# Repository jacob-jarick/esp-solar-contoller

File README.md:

# esp-solar-contoller

esp8266 and esp32 based solar controllers targetting Houses with a fronius solar system (other inverters can be supported).

Inspired by the various DIY powerwalls

https://www.facebook.com/groups/diypowerwalls/

## Use

Common Day devices:

* Pool Pump
* powerwall / UPS / Battery Bank charger
* roof exhuast fan

Common Night time Devices:

* UPS mains disconnect
* Grid tie inverter turn on

## Example Applications

**Simple**

(day) Turn on day time device when PV export is greater than device size (eg pool pump)

**DIY Powerwall**

(Day) Turn on charger when PV export is greater than charger size.

(night) Turn on inverter when power import is larger than inverter size.

**UPS**

(Day) Turn on charger when PV export is greater than charger size.

(night) disconnect UPS mains if house is drawing power from the grid.

## Features

* Self hosted solution, no external servers needed everything runs on the microchip.
* Complete Web Interface for confguration and monitoring.
* JSON config file for easy manual editing.
* OLED display
* Support querying Fronius inverters directly
* NTP time sync
* Fallback WiFi network settings.

### Battery Monitoring (esp32)

* High voltage disconect (day)
* Low Cell Voltage disconnect (night)
* High temp shutdown

## esp8266

Supporrt for all common esp8266 boards.

* sonoff
* IoT Yunshun
* Anything tasmota runs on.

Supports adding OLED display the above.

## ESP32 Board

Custom designed board.

* 16 Bit 4 channel ADC fed to 4 8x analog signal multiplexers allowing for a total of 32 analog lines.

* 16 Voltage monitoring lines.
* 16 ntc temp sensors + 1 ambient temp sensor.
* SD Card for config storage.
* Simple Oled display.
* Piezo buzzer.
* 5v & 3.3v i2c headers for expansion.

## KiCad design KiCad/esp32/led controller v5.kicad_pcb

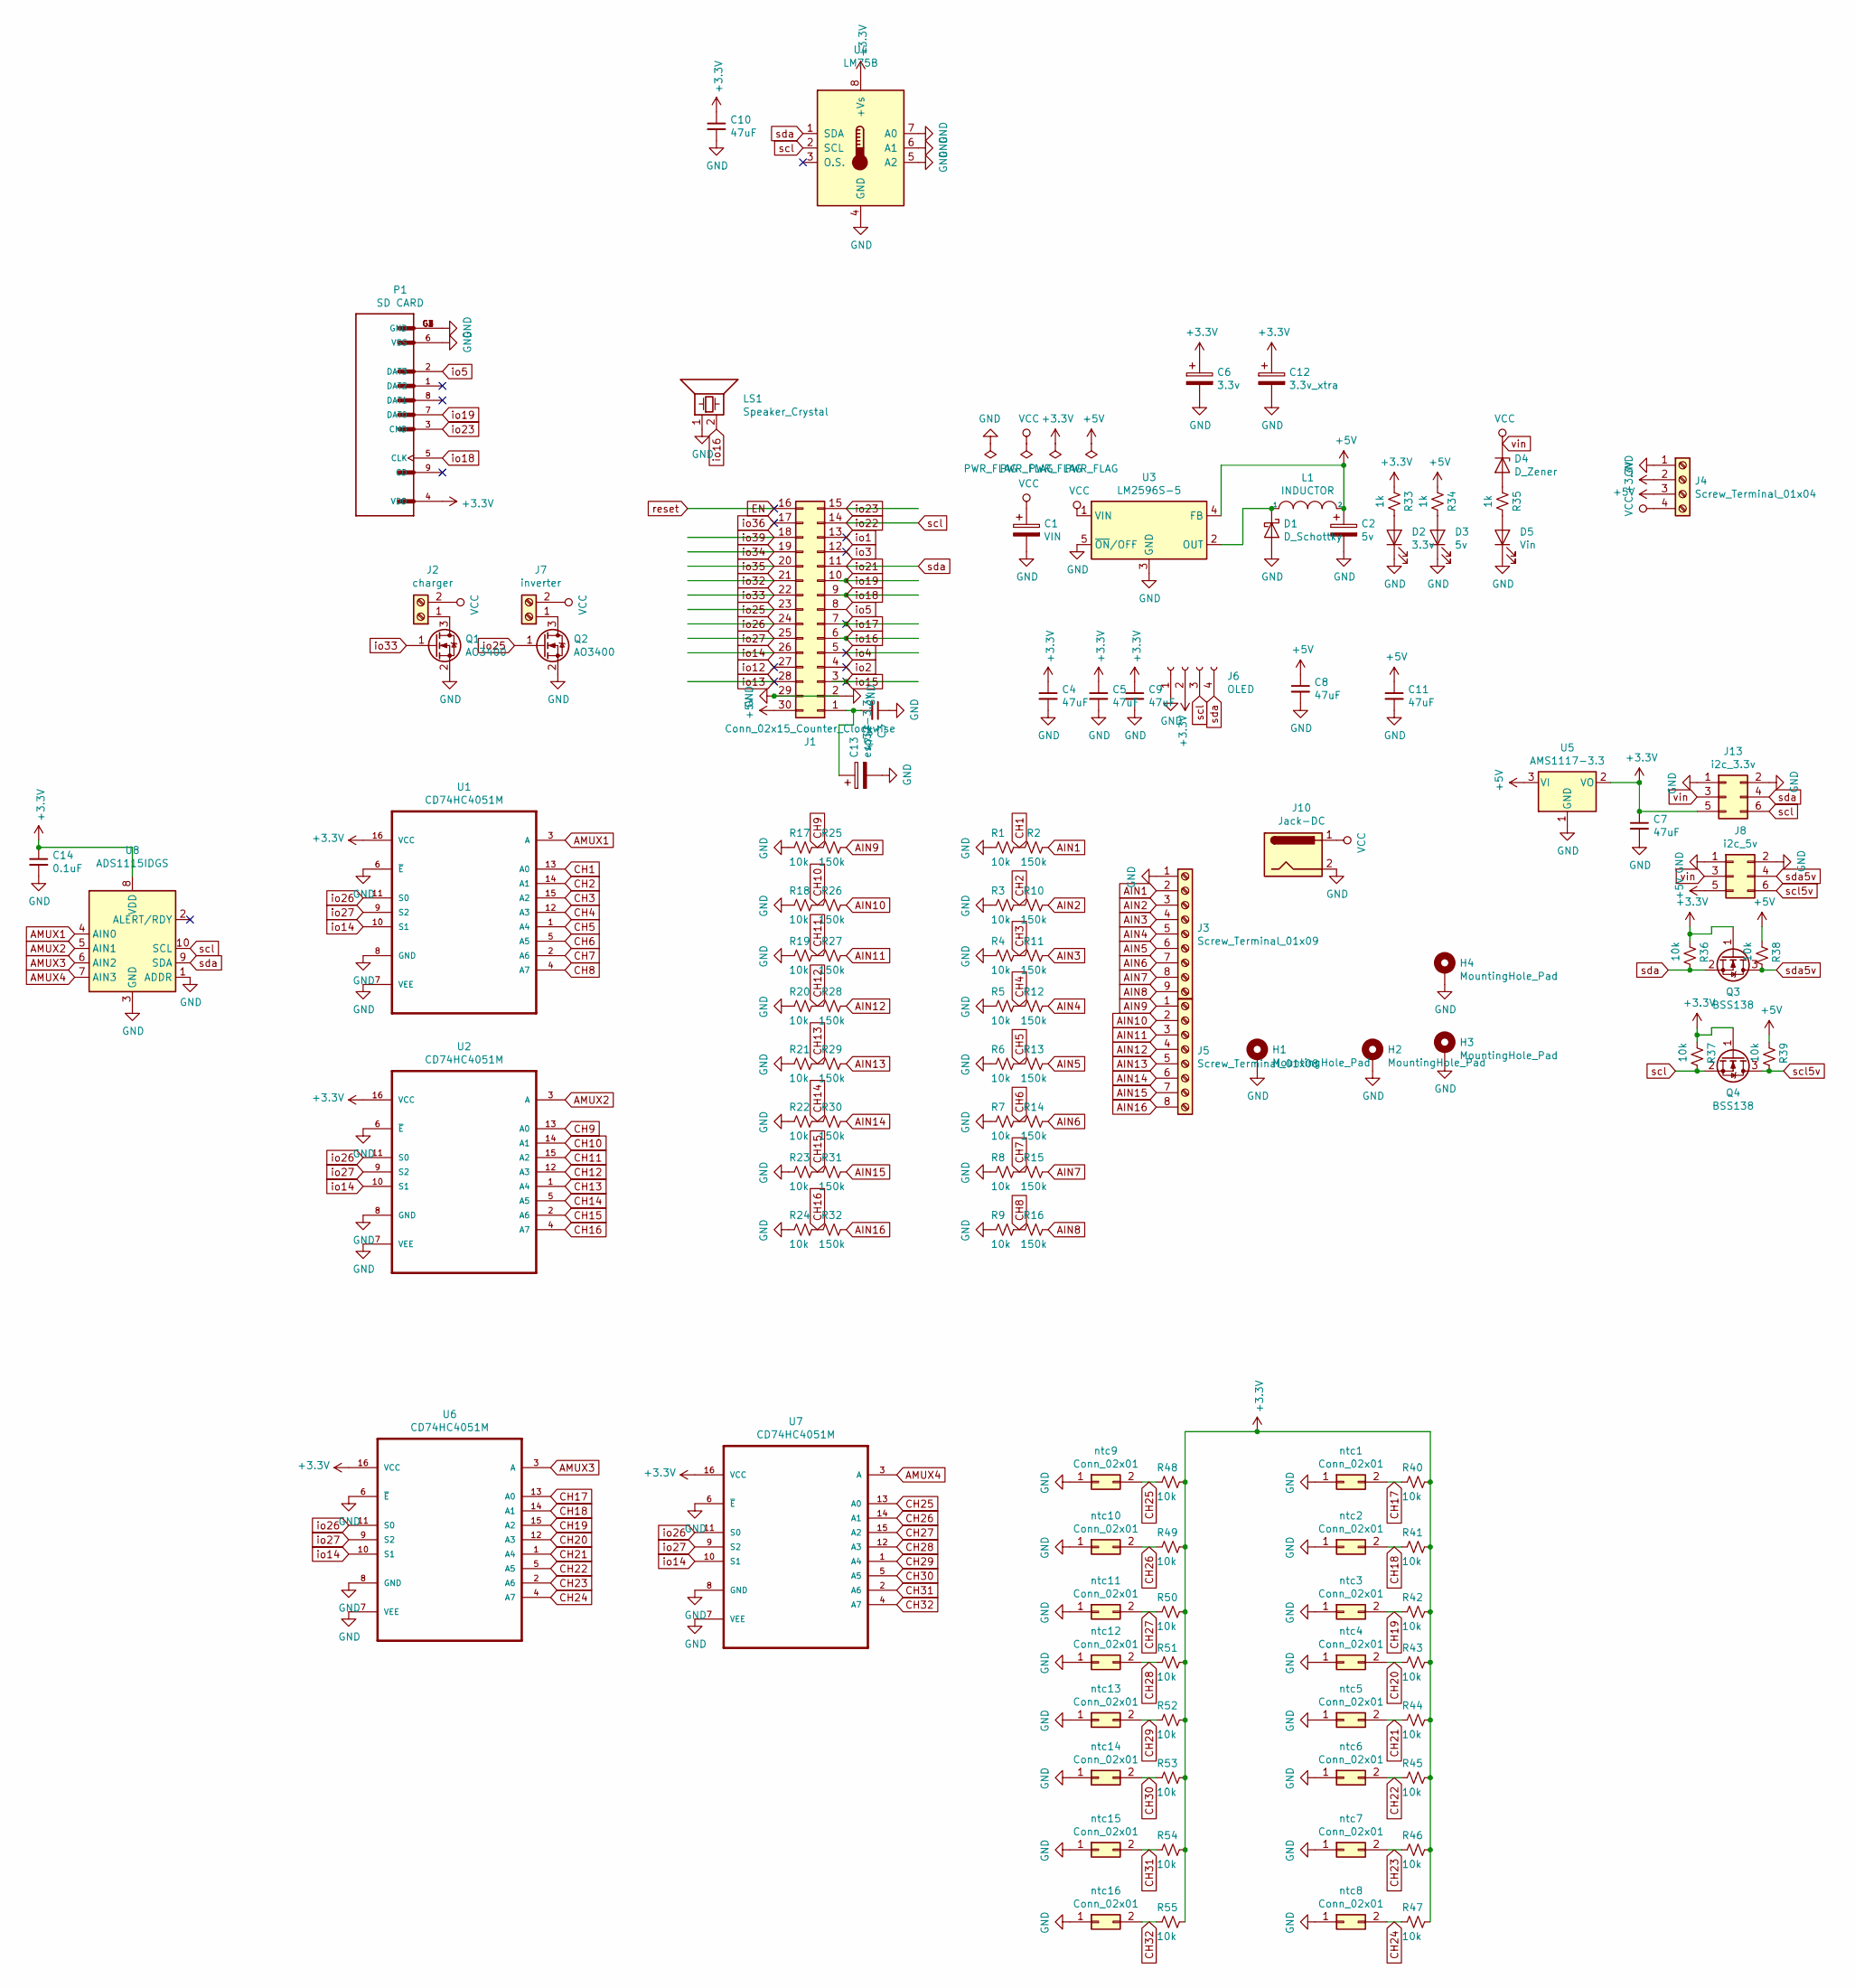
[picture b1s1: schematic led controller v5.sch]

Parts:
C1: VIN; CP_Radial_D10.0mm_P7.50mm
C2: 5v; CP_Radial_D10.0mm_P7.50mm
C3, C4, C5, C7, C8, C9, C10, C11: 47uF; C_0805_2012Metric_Pad1.15x1.40mm_HandSolder
C6: 3.3v; CP_Radial_D10.0mm_P7.50mm
C12: 3.3v_xtra; CP_Radial_D10.0mm_P7.50mm
C13: esp32-3.3v; CP_Radial_D10.0mm_P7.50mm
C14: 0.1uF; C_0805_2012Metric_Pad1.15x1.40mm_HandSolder
D1: D_Schottky; D_SMA_Handsoldering
D2: 3.3v; LED_1206_3216Metric_Pad1.42x1.75mm_HandSolder
D3: 5v; LED_1206_3216Metric_Pad1.42x1.75mm_HandSolder
D4: D_Zener; D_SOD-323F
D5: Vin; LED_1206_3216Metric_Pad1.42x1.75mm_HandSolder
H1, H2, H3, H4: MountingHole_Pad; MountingHole_3.2mm_M3_Pad_Via
J1: Conn_02x15_Counter_Clockwise; esp32-devkit-v1
J2: charger; PhoenixContact_MCV_1,5_2-G-3.81_1x02_P3.81mm_Vertical
J3: Screw_Terminal_01x09; PhoenixContact_MCV_1,5_9-G-3.81_1x09_P3.81mm_Vertical
J4: Screw_Terminal_01x04; PhoenixContact_MCV_1,5_4-G-3.81_1x04_P3.81mm_Vertical
J5: Screw_Terminal_01x08; PhoenixContact_MCV_1,5_8-G-3.81_1x08_P3.81mm_Vertical
J6: OLED; PinHeader_1x04_P2.54mm_Vertical
J7: inverter; PhoenixContact_MCV_1,5_2-G-3.81_1x02_P3.81mm_Vertical
J8: i2c_5v; i2c-Header-5v
J10: Jack-DC; BarrelJack_Horizontal
J13: i2c_3.3v; i2c-Header
L1: INDUCTOR; L_Taiyo-Yuden_MD-5050
LS1: Speaker_Crystal; Buzzer_15x7.5RM7.6
P1: SD CARD; SUNTECH_ST-TF-003A
Q1, Q2: AO3400; SOT-23
Q3, Q4: BSS138; SOT-23
R1, R3, R4, R5, R6, R7, R8, R9, R17, R18, R19, R20, R21, R22, R23, R24, R36, R37, R38, R39, R40, R41, R42, R43, R44, R45, R46, R47, R48, R49, R50, R51, R52, R53, R54, R55: 10k; R_0805_2012Metric_Pad1.15x1.40mm_HandSolder
R2, R10, R11, R12, R13, R14, R15, R16, R25, R26, R27, R28, R29, R30, R31, R32: 150k; R_0805_2012Metric_Pad1.15x1.40mm_HandSolder
R33, R34, R35: 1k; R_0805_2012Metric_Pad1.15x1.40mm_HandSolder
U1, U2, U6, U7: CD74HC4051M; STC_SOP-16_3.9x9.9mm_P1.27mm
U3: LM2596S-5; TO-263-5_TabPin3
U4: LM75B; SOIC-8_3.9x4.9mm_P1.27mm
U5: AMS1117-3.3; SOT-223-3_TabPin2
U8: ADS1115IDGS; TSSOP-10_3x3mm_P0.5mm
ntc1, ntc2, ntc3, ntc4, ntc5, ntc6, ntc7, ntc8, ntc9, ntc10, ntc11, ntc12, ntc13, ntc14, ntc15, ntc16: Conn_02x01; PinHeader_1x02_P2.54mm_Vertical

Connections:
+3V3: C4.1, C5.1, C6.1, C7.1, C9.1, C10.1, C12.1, C14.1, J4.2, J6.2, J13.5, P1.4 (VDD), Q3.1 (G), Q4.1 (G), R33.1, R36.2, R37.2, R40.1, R41.1, R42.1, R43.1, R44.1, R45.1, R46.1, R47.1, R48.1, R49.1, R50.1, R51.1, R52.1, R53.1, R54.1, R55.1, U1.16 (VCC), U2.16 (VCC), U4.8 (+Vs), U5.2 (VO), U6.16 (VCC), U7.16 (VCC), U8.8 (VDD)
+5V: C2.1, C8.1, C11.1, J1.30, J4.3, J8.5, L1.2, R34.1, R38.2, R39.2, U3.4 (FB), U5.3 (VI)
AIN1: J3.2, R2.2
AIN2: J3.3, R10.2
AIN3: J3.4, R11.2
AIN4: J3.5, R12.2
AIN5: J3.6, R13.2
AIN6: J3.7, R14.2
AIN7: J3.8, R15.2
AIN8: J3.9, R16.2
AIN9: J5.1, R25.2
AIN10: J5.2, R26.2
AIN11: J5.3, R27.2
AIN12: J5.4, R28.2
AIN13: J5.5, R29.2
AIN14: J5.6, R30.2
AIN15: J5.7, R31.2
AIN16: J5.8, R32.2
AMUX1: U1.3 (A), U8.4 (AIN0)
AMUX2: U2.3 (A), U8.5 (AIN1)
AMUX3: U6.3 (A), U8.6 (AIN2)
AMUX4: U7.3 (A), U8.7 (AIN3)
CH1: R1.1, R2.1, U1.13 (A0)
CH2: R3.1, R10.1, U1.14 (A1)
CH3: R4.1, R11.1, U1.15 (A2)
CH4: R5.1, R12.1, U1.12 (A3)
CH5: R6.1, R13.1, U1.1 (A4)
CH6: R7.1, R14.1, U1.5 (A5)
CH7: R8.1, R15.1, U1.2 (A6)
CH8: R9.1, R16.1, U1.4 (A7)
CH9: R17.1, R25.1, U2.13 (A0)
CH10: R18.1, R26.1, U2.14 (A1)
CH11: R19.1, R27.1, U2.15 (A2)
CH12: R20.1, R28.1, U2.12 (A3)
CH13: R21.1, R29.1, U2.1 (A4)
CH14: R22.1, R30.1, U2.5 (A5)
CH15: R23.1, R31.1, U2.2 (A6)
CH16: R24.1, R32.1, U2.4 (A7)
CH17: R40.2, U6.13 (A0), ntc1.2
CH18: R41.2, U6.14 (A1), ntc2.2
CH19: R42.2, U6.15 (A2), ntc3.2
CH20: R43.2, U6.12 (A3), ntc4.2
CH21: R44.2, U6.1 (A4), ntc5.2
CH22: R45.2, U6.5 (A5), ntc6.2
CH23: R46.2, U6.2 (A6), ntc7.2
CH24: R47.2, U6.4 (A7), ntc8.2
CH25: R48.2, U7.13 (A0), ntc9.2
CH26: R49.2, U7.14 (A1), ntc10.2
CH27: R50.2, U7.15 (A2), ntc11.2
CH28: R51.2, U7.12 (A3), ntc12.2
CH29: R52.2, U7.1 (A4), ntc13.2
CH30: R53.2, U7.5 (A5), ntc14.2
CH31: R54.2, U7.2 (A6), ntc15.2
CH32: R55.2, U7.4 (A7), ntc16.2
EN: J1.16
GND: C1.2, C2.2, C3.1, C4.2, C5.2, C6.2, C7.2, C8.2, C9.2, C10.2, C11.2, C12.2, C13.2, C14.2, D1.2 (A), D2.1 (K), D3.1 (K), D5.1 (K), H1.1, H2.1, H3.1, H4.1, J1.2, J1.29, J3.1, J4.1, J6.1, J8.1, J8.2, J10.2, J13.1, J13.2, LS1.1, P1.6 (VSS), P1.G1 (GND), P1.G2 (GND), P1.G3 (GND), P1.G4 (GND), Q1.2 (S), Q2.2 (S), R1.2, R3.2, R4.2, R5.2, R6.2, R7.2, R8.2, R9.2, R17.2, R18.2, R19.2, R20.2, R21.2, R22.2, R23.2, R24.2, U1.6 (~E), U1.7 (VEE), U1.8 (GND), U2.6 (~E), U2.7 (VEE), U2.8 (GND), U3.3 (GND), U3.5 (~ON~/OFF), U4.4 (GND), U4.5 (A2), U4.6 (A1), U4.7 (A0), U5.1 (GND), U6.6 (~E), U6.7 (VEE), U6.8 (GND), U7.6 (~E), U7.7 (VEE), U7.8 (GND), U8.1 (ADDR), U8.3 (GND), ntc1.1, ntc2.1, ntc3.1, ntc4.1, ntc5.1, ntc6.1, ntc7.1, ntc8.1, ntc9.1, ntc10.1, ntc11.1, ntc12.1, ntc13.1, ntc14.1, ntc15.1, ntc16.1
unnamed: C3.2, C13.1, J1.1
unnamed: D1.1 (K), L1.1, U3.2 (OUT)
unnamed: D2.2 (A), R33.2
unnamed: D3.2 (A), R34.2
unnamed: D4.2 (A), R35.1
unnamed: D5.2 (A), R35.2
unnamed: J2.1, Q1.3 (D)
unnamed: J7.1, Q2.3 (D)
io1: J1.13
io2: J1.4
io3: J1.12
io4: J1.5
io5: J1.8, P1.2 (DAT3)
io12: J1.27
io13: J1.28
io14: J1.26, U1.10 (S1), U2.10 (S1), U6.10 (S1), U7.10 (S1)
io15: J1.3
io16: J1.6, LS1.2
io17: J1.7
io18: J1.9, P1.5 (CLK)
io19: J1.10, P1.7 (DAT0)
io21: J1.11, J6.4, J13.4, Q3.2 (S), R36.1, U4.1 (SDA), U8.9 (SDA)
io22: J1.14, J6.3, J13.6, Q4.2 (S), R37.1, U4.2 (SCL), U8.10 (SCL)
io23: J1.15, P1.3 (CMD)
io25: J1.23, Q2.1 (G)
io26: J1.24, U1.11 (S0), U2.11 (S0), U6.11 (S0), U7.11 (S0)
io27: J1.25, U1.9 (S2), U2.9 (S2), U6.9 (S2), U7.9 (S2)
io32: J1.21
io33: J1.22, Q1.1 (G)
io34: J1.19
io35: J1.20
io36: J1.17
io39: J1.18
scl5v: J8.6, Q4.3 (D), R39.1
sda5v: J8.4, Q3.3 (D), R38.1
vin: C1.1, D4.1 (K), J2.2, J4.4, J7.2, J8.3, J10.1, J13.3, U3.1 (VIN)

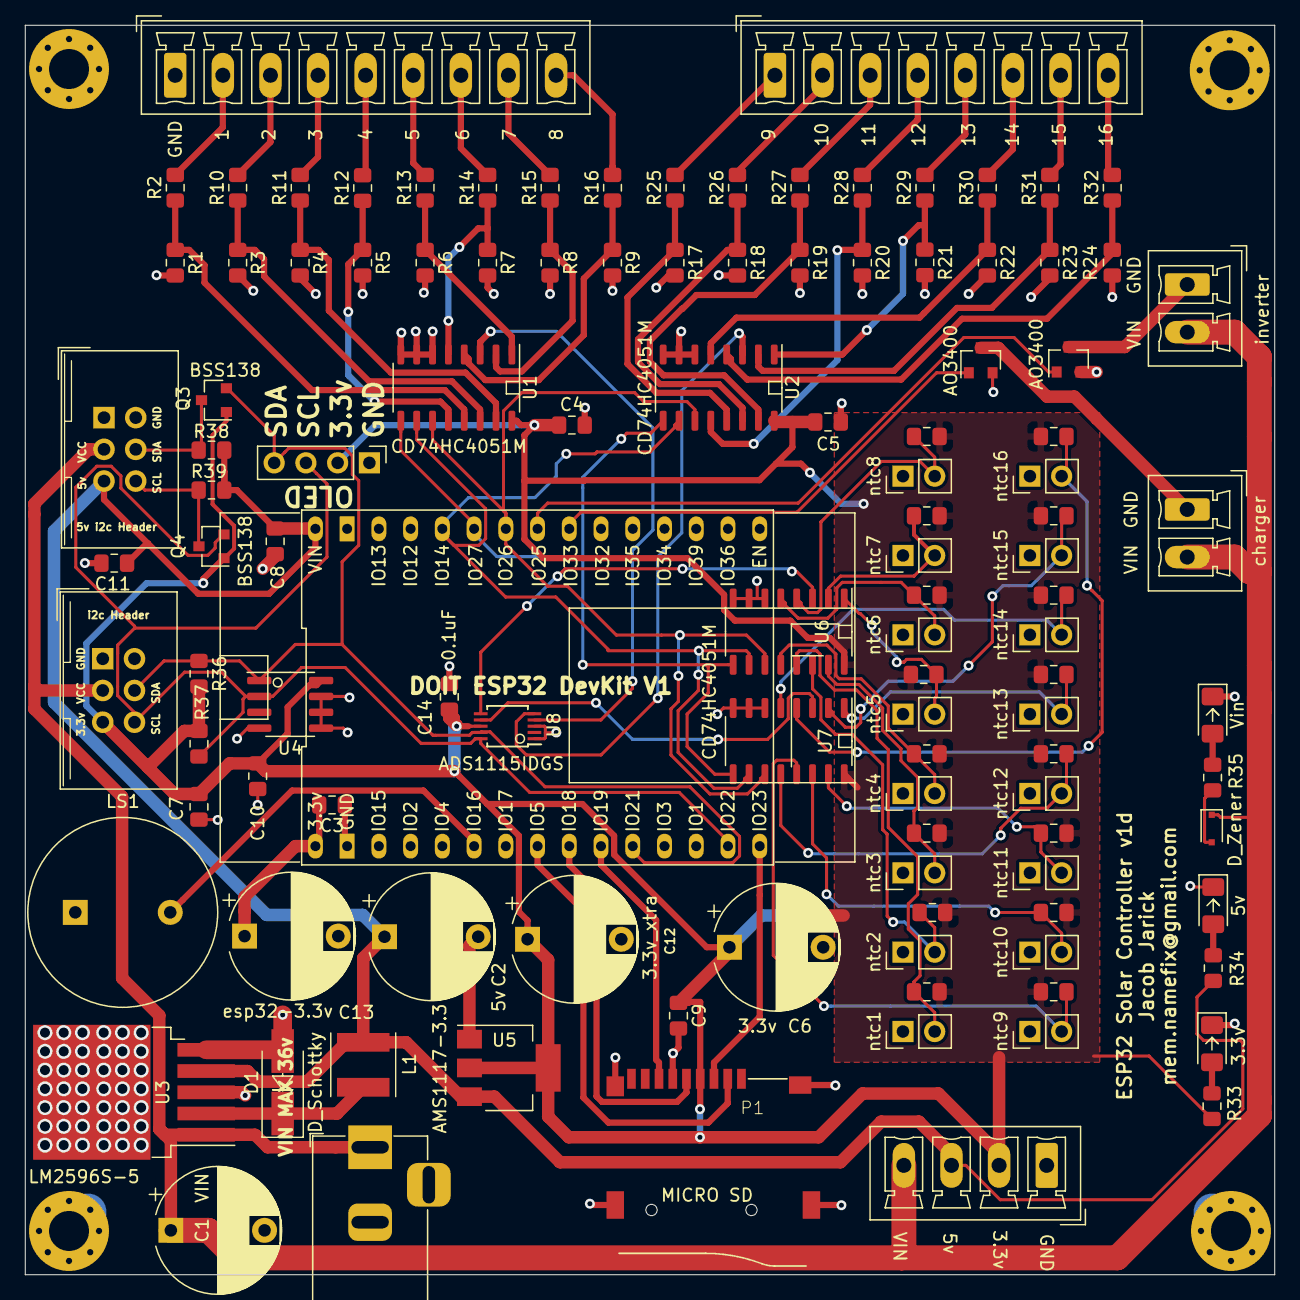
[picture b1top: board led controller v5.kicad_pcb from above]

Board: 2 copper layers, 100.0 x 100.0 mm, 119 parts (0 on the bottom side), 78 nets.

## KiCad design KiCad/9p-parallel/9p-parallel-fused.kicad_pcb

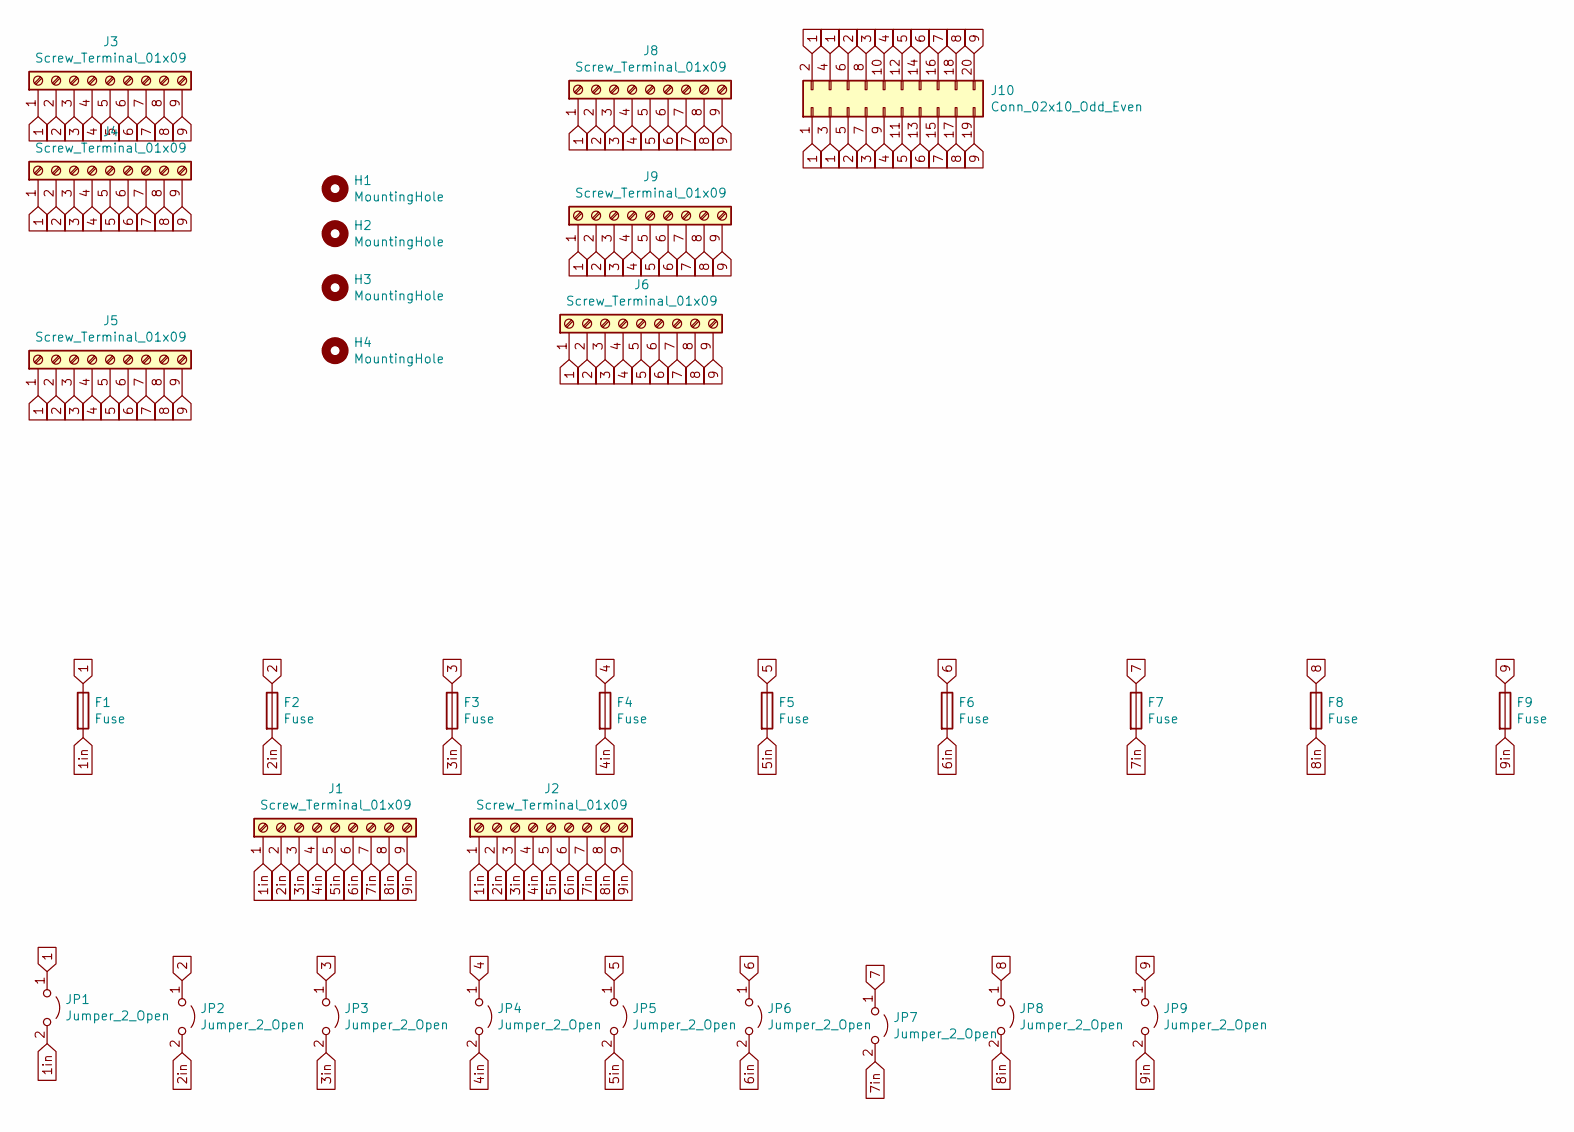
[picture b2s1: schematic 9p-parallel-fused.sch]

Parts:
F1, F2, F3, F4, F5, F6, F7, F8, F9: Fuse; Fuseholder_Cylinder-5x20mm_Stelvio-Kontek_PTF78_Horizontal_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
H1, H2, H3, H4: MountingHole; MountingHole_4.3mm_M4_ISO14580
J1: Screw_Terminal_01x09; PhoenixContact_MC_1,5_9-G-5.08_1x09_P5.08mm_Horizontal-larg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
J2, J6, J8, J9: Screw_Terminal_01x09; PhoenixContact_MCV_1,5_9-G-3.81_1x09_P3.81mm_Vertical
J3, J4, J5: Screw_Terminal_01x09; PhoenixContact_MCV_1,5_9-G-5.08_1x09_P5.08mm_Vertical-large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
J10: Conn_02x10_Odd_Even; IDC-Header_2x10_P2.54mm_Vertical
JP1, JP2, JP3, JP4, JP5, JP6, JP7, JP8, JP9: Jumper_2_Open; SolderJumper-2_P1.3mm_Open_Pad1.0x1.5mm

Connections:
1: F1.1, J3.1, J4.1, J5.1, J6.1, J8.1, J9.1, J10.1, J10.2, J10.3, J10.4, JP1.1 (A)
1in: F1.2, J1.1, J2.1, JP1.2 (B)
2: F2.1, J3.2, J4.2, J5.2, J6.2, J8.2, J9.2, J10.5, J10.6, JP2.1 (A)
2in: F2.2, J1.2, J2.2, JP2.2 (B)
3: F3.1, J3.3, J4.3, J5.3, J6.3, J8.3, J9.3, J10.7, J10.8, JP3.1 (A)
3in: F3.2, J1.3, J2.3, JP3.2 (B)
4: F4.1, J3.4, J4.4, J5.4, J6.4, J8.4, J9.4, J10.9, J10.10, JP4.1 (A)
4in: F4.2, J1.4, J2.4, JP4.2 (B)
5: F5.1, J3.5, J4.5, J5.5, J6.5, J8.5, J9.5, J10.11, J10.12, JP5.1 (A)
5in: F5.2, J1.5, J2.5, JP5.2 (B)
6: F6.1, J3.6, J4.6, J5.6, J6.6, J8.6, J9.6, J10.13, J10.14, JP6.1 (A)
6in: F6.2, J1.6, J2.6, JP6.2 (B)
7: F7.1, J3.7, J4.7, J5.7, J6.7, J8.7, J9.7, J10.15, J10.16, JP7.1 (A)
7in: F7.2, J1.7, J2.7, JP7.2 (B)
8: F8.1, J3.8, J4.8, J5.8, J6.8, J8.8, J9.8, J10.17, J10.18, JP8.1 (A)
8in: F8.2, J1.8, J2.8, JP8.2 (B)
9: F9.1, J3.9, J4.9, J5.9, J6.9, J8.9, J9.9, J10.19, J10.20, JP9.1 (A)
9in: F9.2, J1.9, J2.9, JP9.2 (B)

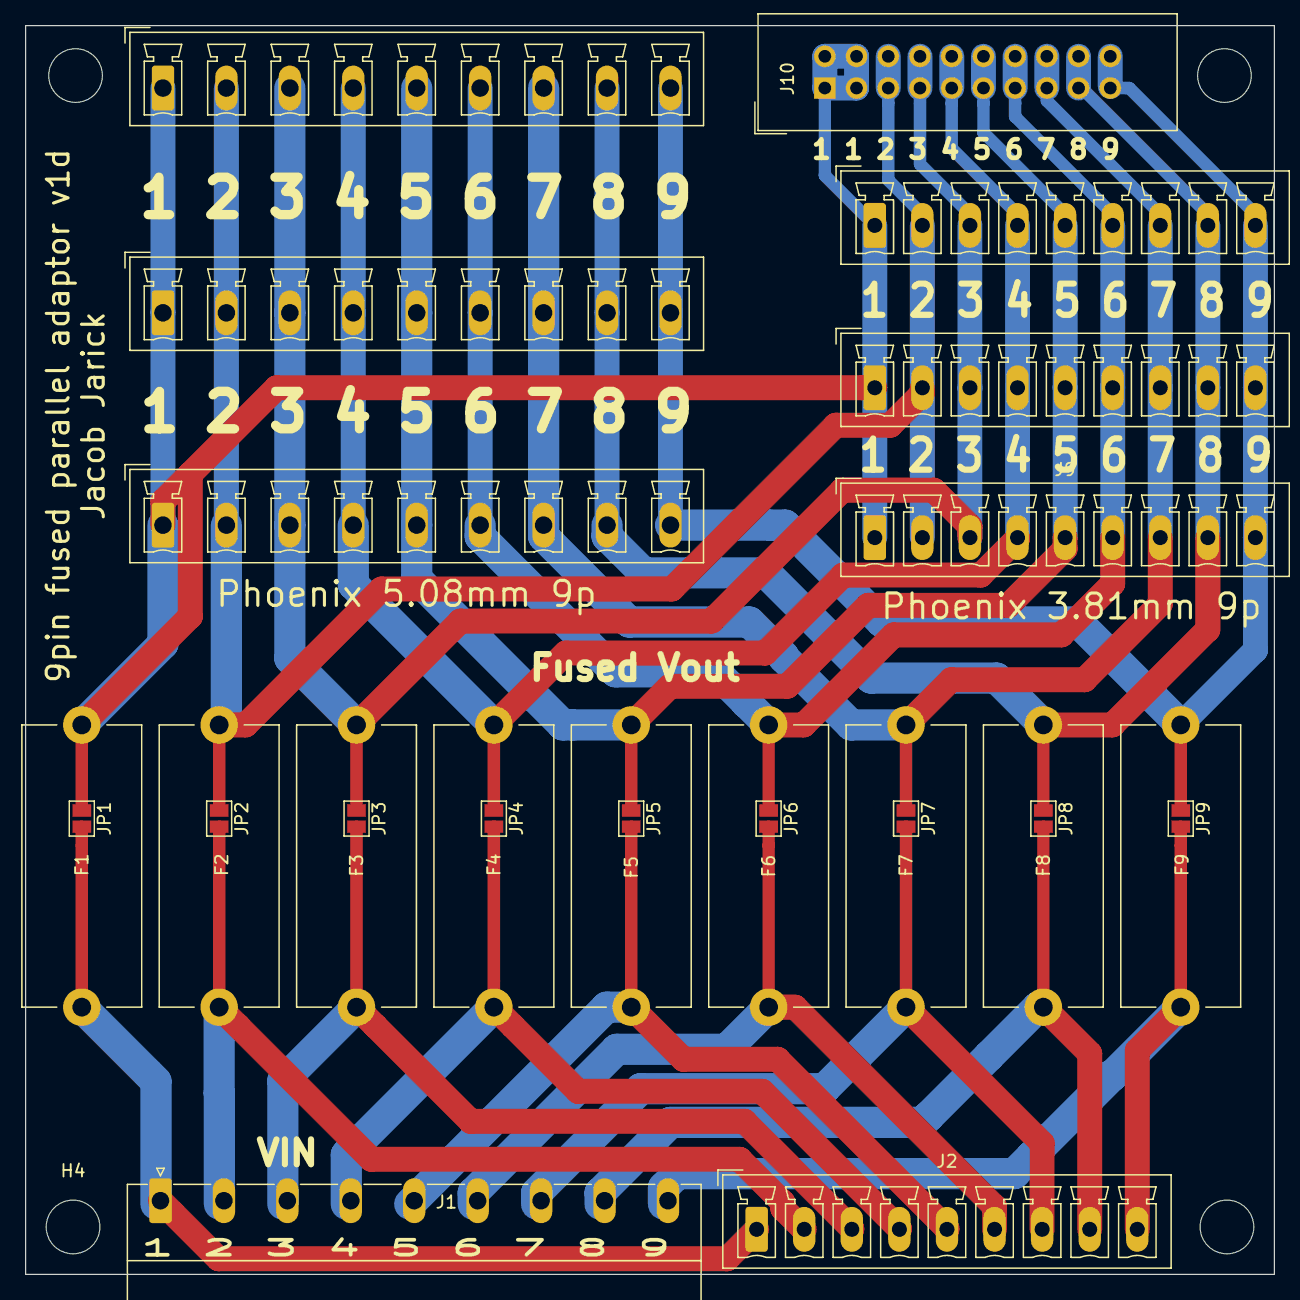
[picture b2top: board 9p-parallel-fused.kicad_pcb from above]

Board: 2 copper layers, 100.0 x 100.0 mm, 31 parts (0 on the bottom side), 18 nets.

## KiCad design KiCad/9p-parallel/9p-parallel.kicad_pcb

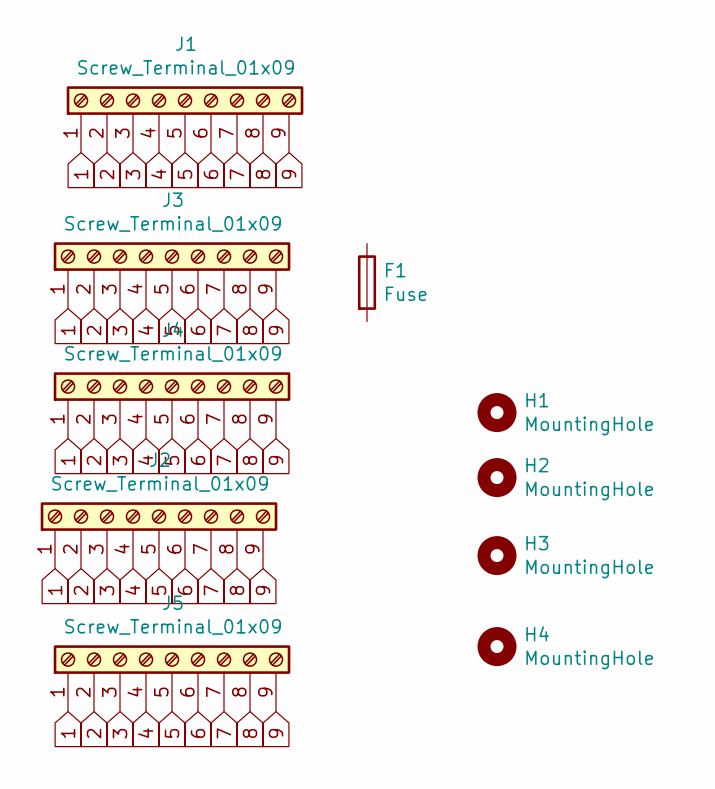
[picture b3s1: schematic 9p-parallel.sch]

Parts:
F1: Fuse; Fuseholder_Cylinder-5x20mm_Stelvio-Kontek_PTF78_Horizontal_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
H1, H2, H3, H4: MountingHole; MountingHole_4.3mm_M4_ISO14580
J1: Screw_Terminal_01x09; PhoenixContact_MC_1,5_9-G-5.08_1x09_P5.08mm_Horizontal
J2, J3, J4, J5: Screw_Terminal_01x09; PhoenixContact_MCV_1,5_9-G-5.08_1x09_P5.08mm_Vertical

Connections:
1: J1.1, J2.1, J3.1, J4.1, J5.1
2: J1.2, J2.2, J3.2, J4.2, J5.2
3: J1.3, J2.3, J3.3, J4.3, J5.3
4: J1.4, J2.4, J3.4, J4.4, J5.4
5: J1.5, J2.5, J3.5, J4.5, J5.5
6: J1.6, J2.6, J3.6, J4.6, J5.6
7: J1.7, J2.7, J3.7, J4.7, J5.7
8: J1.8, J2.8, J3.8, J4.8, J5.8
9: J1.9, J2.9, J3.9, J4.9, J5.9

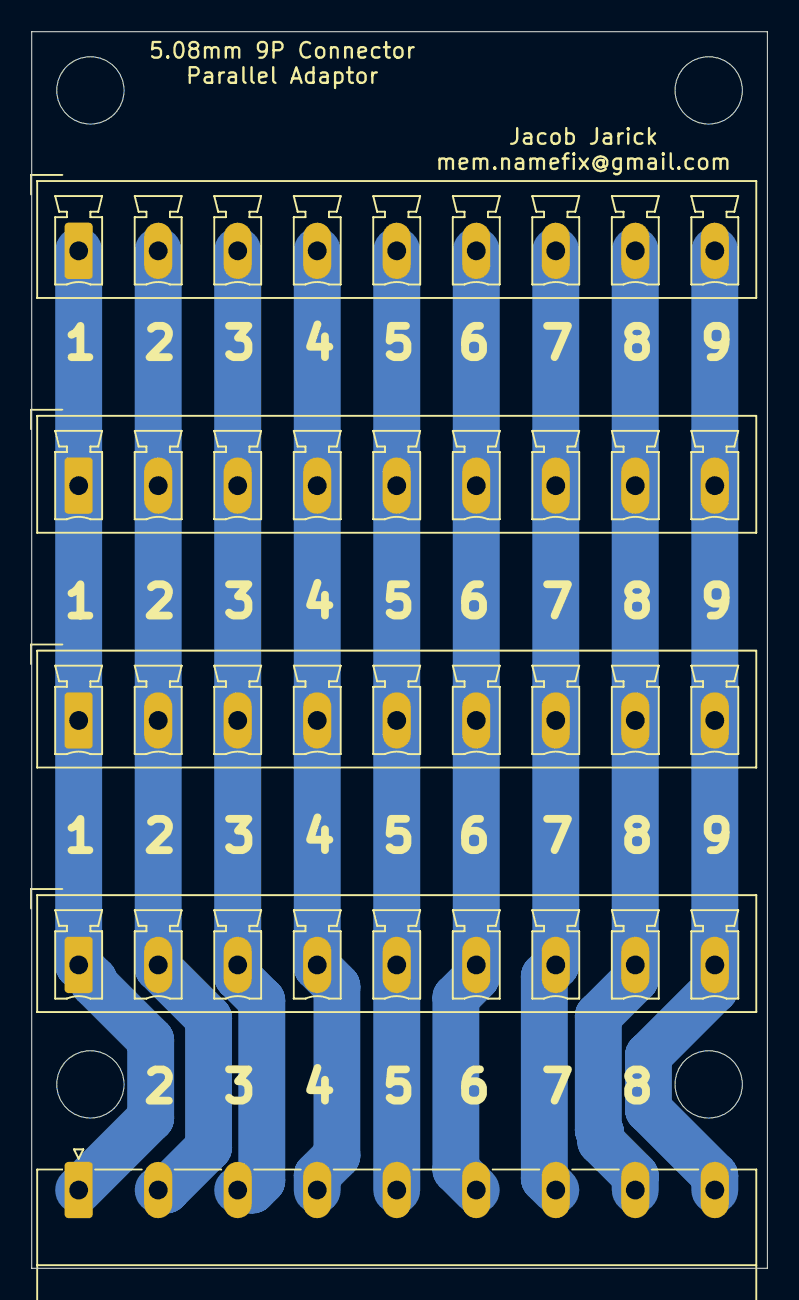
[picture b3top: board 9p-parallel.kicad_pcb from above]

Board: 2 copper layers, 47.0 x 79.0 mm, 9 parts (0 on the bottom side), 9 nets.

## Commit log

2020-02-28 source push
2020-02-28 shell scripts
2020-02-28 added shell scripts for publishing firmwares
2020-02-28 tidy up
2020-02-28 tidy
2020-03-02 update code for ads1115.
2020-03-02 adc code, html examples
2020-03-02 fixes to support latest esp32 arduino release.
    adc - set gain etc after inlcude ads11115
    ESP32HTTPUpdate - old httpupdate no longer works, fixes applied.
    maths - float_max - ESP32HTTPUpdate (among others) undef Arduino min and max. easiest fix is to provide my own function.
    webpages - toDouble not a string member anymore ? or never was. fixed.
    HTTPClient - argument syntax has changed for esp32 lib - fixed.
2020-03-03 cleanup
2020-03-03 update.ino - fix html loop if unable to fetch file
2020-03-05 consts
2020-03-06 i2c is buggy on latest board. slowed down bus speed
2020-03-06 ntc stuff
2020-03-06 ntc work
2020-03-07 ntc fix
2020-03-07 adc battery fix
2020-03-07 networking fixes.
2020-03-07 update logic, adc, ports, save config optimization
2020-03-13 battery calibration
2020-03-15 battery + temp
    battery calibration page added.
    ntc temp max changed to uint8_t
2020-03-15 maths max, ping sd, night time logic
2020-03-16 24/7 mode added
    same as setting charger and inverter time slots to 12-12
2020-03-16 update html fix
2020-03-16 battery calibrate JS moved to battery page
2020-03-16 updated ESP32 board
2020-03-16 images
2020-03-16 Update esp32_solar_controller.ino
    24/7 - idle between device swaps.
    mode reason message text cleaned up
2020-03-16 removing msg.txt
2020-03-16 remove all traces of frline
    handy for esp8266 due to lack of progmem space, for esp32 it just makes things harder to follow.
2020-03-16 latest firmware
2020-03-17 modeset fix
2020-03-18 consts, mode message
2020-03-29 fsfree removed, random delays added for same mode
2020-03-30 removed pcf support. small tidy up
2020-03-31 battery_msg removed.
2020-03-31 fixes
2020-03-31 system_msgs
2020-03-31 size_system_msgs
2020-04-01 download_html
    trigger if FW versions are different.
    moved bool to flags from config.
2020-04-01 type fix
2020-04-02 get_url & get_url_and_save
2020-04-02 fronius fix
2020-04-02 strings
2020-04-09 adc polling
    much more efficient ADC checking.
2020-04-09 adc poll timer
2020-04-09 rm volt_synced flag
2020-04-09 phase voltage monitoring
2020-04-09 idle fix
2020-04-09 maths, time.
2020-04-09 time compare fix
2020-04-09 overflow fix
2020-04-10 remove adc_read
    access array directly
2020-04-10 adc_enable
    skip ADC reads on disabled channels
2020-04-10 adc_enable
2020-04-12 removed battery_volt_idl & battery_volt_over
2020-04-12 latest fw
2020-04-12 fronius 3phase work
2020-04-19 QuickMedianLib
2020-05-04 Ads1115_mux lib
2020-05-04 Ads1115_mux library
    WIP.
    compiles clean.
2020-05-04 Ads1115_mux
2020-05-08 remove QuickMedianLib dep
    using bubble sort
2020-05-08 Ads1115_mux optmizations
2020-05-08 Ads1115_mux::digital_write
2020-05-08 var cleanup
2020-05-09 maths to libary
2020-05-09 shutdown_htemp optimization
2020-05-11 rm ntc_temp_mods
    accurate enough, also makes config.jsn smaller
    extra msg info
2020-05-12 html cleanup
2020-05-18 arduino JSON lib update
2020-06-01 lm75a code added
2020-06-01 lm75a temp displayed on oled
2020-07-08 warnings and docs
2020-07-19 ads1015 support added
2020-07-30 messages
2020-08-03 micro board. esp8266 firmware refresh
2020-08-05 fw 27
2020-08-10 bool adc_found
2020-08-10 f(!adsmux.adc_found)
2020-08-16 Oled Display Options
2020-08-17 led, stats
    fixed led modes.
    added energy display options.
2020-08-17 Cost Per Kwh
2020-08-26 ntc temp, usage tracking
2020-08-26 alarm tweak
2020-08-27 Idle When Export<
2020-08-27 fronius new day tracking
2020-08-31 fronius timestap checks
2020-09-02 tidy update code
2020-09-03 i2c_check
2020-09-03 ADC checks
    if monitor temp or voltage enabled and ADC not found force IDLE.
2020-09-03 fronius time fix
2020-09-03 proper averaging for phase sum
2020-09-11 div by 0 fix
2020-09-23 prefer DC option added
2020-10-04 strings and mode tracking
2020-10-07 favour DC
    updates and tweaks
2020-10-19 fw 183
2020-10-21 force_refresh
2020-10-21 ADC tweak
2020-10-21 web stuff
2020-11-03 fw 188 both_on mode set
2020-11-24 min off time.
    mainly code to support my bore pump.
2020-12-01 HV/ LV msgs
2020-12-01 fw 198 - log manual mode
2020-12-04 docs - diagram
2020-12-04 docs - diagrams
2020-12-15 fw 199
2020-12-15 fw 200
    small update
2021-01-03 fw 201.
    log messages
2021-01-04 mime fixes
2021-01-05 config validation
2021-01-07 syslog hostname
2021-01-11 system messages shifted to footer
2021-01-13 swapped to common header
2021-02-06 libs updated
2021-09-20 working on Lib updates.
2021-09-20 dummy
2021-09-20 dummy2
2021-09-23 fw 228.
    had to roll back o esp32 board libs 1.0.6 - issue with SD card in 2.0.0
2021-09-27 FW 229
    increased analog cell count to 32
    SD_setup.sh
2021-09-27 fix ads1115 setup
2021-09-29 fw 232
    remove hard coded limits to max cell count
2021-09-29 fw 242
    gutted NTC code, has not been used.
2021-10-13 pub url on github
2021-10-13 pub URL
2021-10-13 JSON config pretty print.
    Pub update dir.
2021-10-13 cv.txt
2021-10-13 html download debug
2021-10-19 web formatting
2021-10-26 calc_energy_usage
    moved energy used calculation to its own sub.
    called from check_grid
2021-10-29 fixes, single phase updates.
    get_watts - should work with single phase better
    calc_energy_usage - uses its own timer.
2021-11-06 added new oled display mode
2021-11-06 fw number bump
2021-11-06 3phase/single phase updates
2021-11-06 fw 244
2021-11-06 245
    whitespaces
2021-11-06 number formatting
2021-11-09 fw 247
    mostly whitespace fixes
2021-11-09 fw 247
    mostly white space fixes
2021-11-11 voltage tracking
2021-11-11 fix min AC voltage tracking
2021-11-11 update code cleaned up
2021-11-19 about to break adsmux for mcp3021
2021-11-20 adc mux code update complete..
    backwards compatible with v3 board mux.
    must set ADS1x15type and MUXType in system settings.
2021-11-21 fw 278
2021-11-21 fw 282
2021-11-23 user can toggle ain averaging
2021-11-24 optimize adc mux polling code
2021-11-24 BUGFIX - pin select in adc poll was wonky
2021-11-25 adc code tweaks. esp board libs 2.0.1
2021-11-26 roll back to 1.0.6 of esp32 board libs
    issues with SPI and SD card
2021-11-27 LV disconnect message formatting
2021-12-01 latest
2021-12-01 HV checks more verbose
2021-12-01 systick reduced to 5ms
2021-12-02 adc reads speed up
2021-12-02 speed up again
2021-12-10 optimizations
2021-12-10 code cleanup
    update functions no longer return strings. (yuck)
2022-01-02 small tweak
2022-01-09 added 0x4e address for mcp chip
2022-01-14 bugfix
2022-01-18 support lm75a on microboards
2022-01-18 ambient temp displayed on status
2022-01-19 log overheat and recovery
2022-01-21 status page formatting
2022-01-21 fix mode reason
2022-01-21 track min max amb temp
2022-01-23 api added
2022-01-24 begin multiple api server support
2022-01-24 fw360 - api stuff
2022-01-26 rescued work
2022-01-26 correct local library refs
2022-01-26 errors fixed
2022-01-26 fw bump
2022-01-26 API update - config breakages
2022-01-26 cells check
2022-01-26 bugfix/test
2022-01-26 api fix
2022-01-26 api poller fix
2022-01-26 fw 370
2022-01-26 remove old commented code
2022-01-27 fw 371 - refactoring
2022-01-27 split grid and temp api servers to own group
2022-01-27 374 - bugfix
2022-01-27 375 - config - docv_to_chara
2022-01-27 push update to public
2022-01-27 376
    remove old stuff from api
2022-01-27 377 - pack_total_volts fixup
2022-01-28 update api page
2022-01-28 function table_add_submit(id)
2022-01-30 378 - cleanup fronius
2022-01-30 adc poll tweaks
2022-01-31 fw 380 - muxtype 2
2022-01-31 fix absent fronius_push_url from config
    also renamed since I broke it in the config anyway.
2022-01-31 fw 381
2022-02-10 whitespace
2022-02-20 batcal for precision board
2022-02-25 fw 389
2023-03-28 update shell
2023-03-31 clean compile on latest versions of esp32 base and arduinojson
    also had to patch lm75a lib
2023-04-01 mmaths patch
2023-04-01 anisble fixes and updates
2023-04-02 ansible fixes
2023-04-02 merging branch.
2023-04-02 added Adams feature request
2023-04-02 mode setting update 2
    rolled functions into 1
2023-04-22 NTP update
    also lib & board update
2023-04-24 home automation stuff
2023-04-25 added switch for HASS
2023-04-25 expose pin mode in api
2023-04-25 more automation
2023-04-26 HASS stuff
2023-05-19 esp32 board fw update, html fix
2024-05-12 updated ansible stuff
2024-11-18 migrate to board libs 3.0
    pwm fixed
2024-11-18 Updating to boards library 3.0
    AP Mode Fixed
2024-11-20 beep fixed !
2024-11-20 no longer using DynamicJsonDocument
    was a straight swap from DynamicJsonDocument to JsonDocument
    just had to remove the config_json_size
2024-11-20 removed jsonsize
2024-11-20 containsKey
    old:
    doc.containsKey("key")
    new:
    doc["key"].is<JsonVariant>()
2024-11-26 new FW
